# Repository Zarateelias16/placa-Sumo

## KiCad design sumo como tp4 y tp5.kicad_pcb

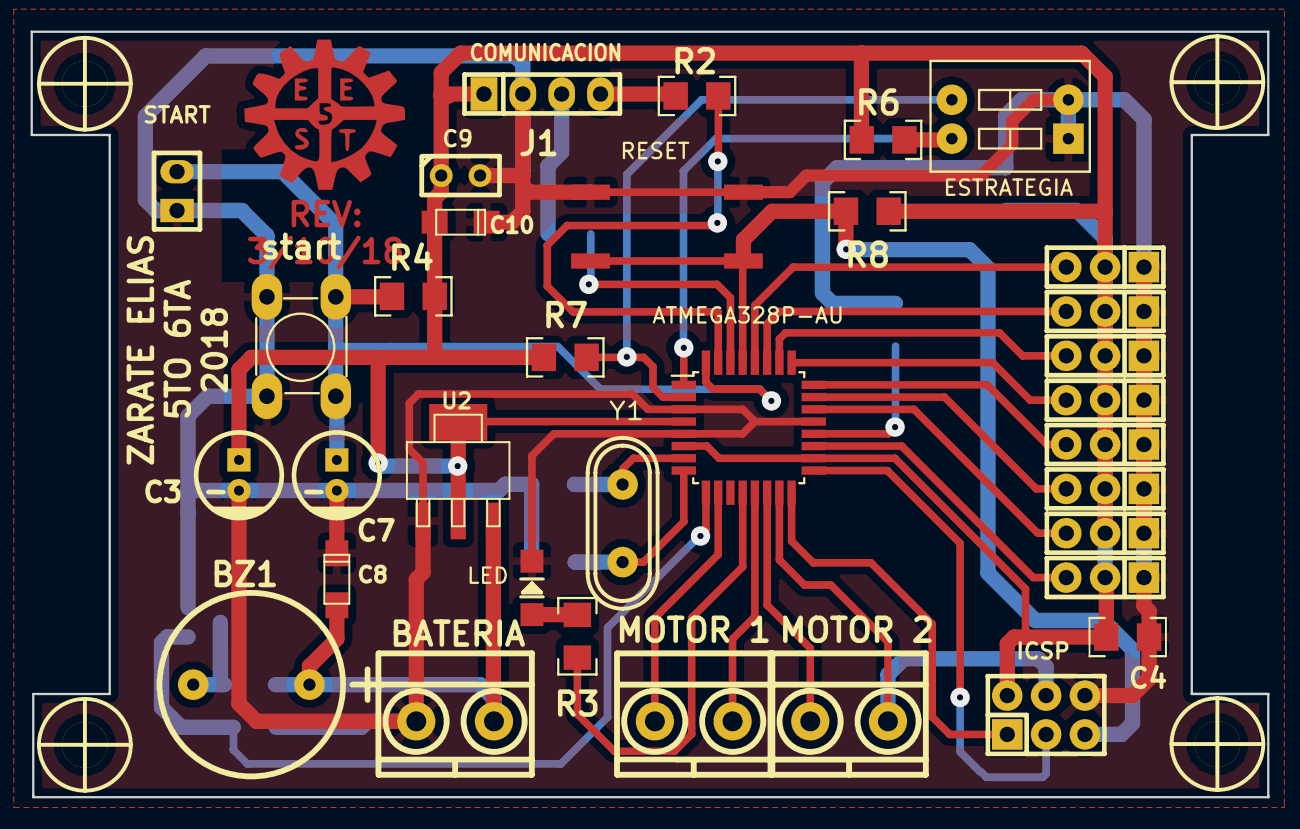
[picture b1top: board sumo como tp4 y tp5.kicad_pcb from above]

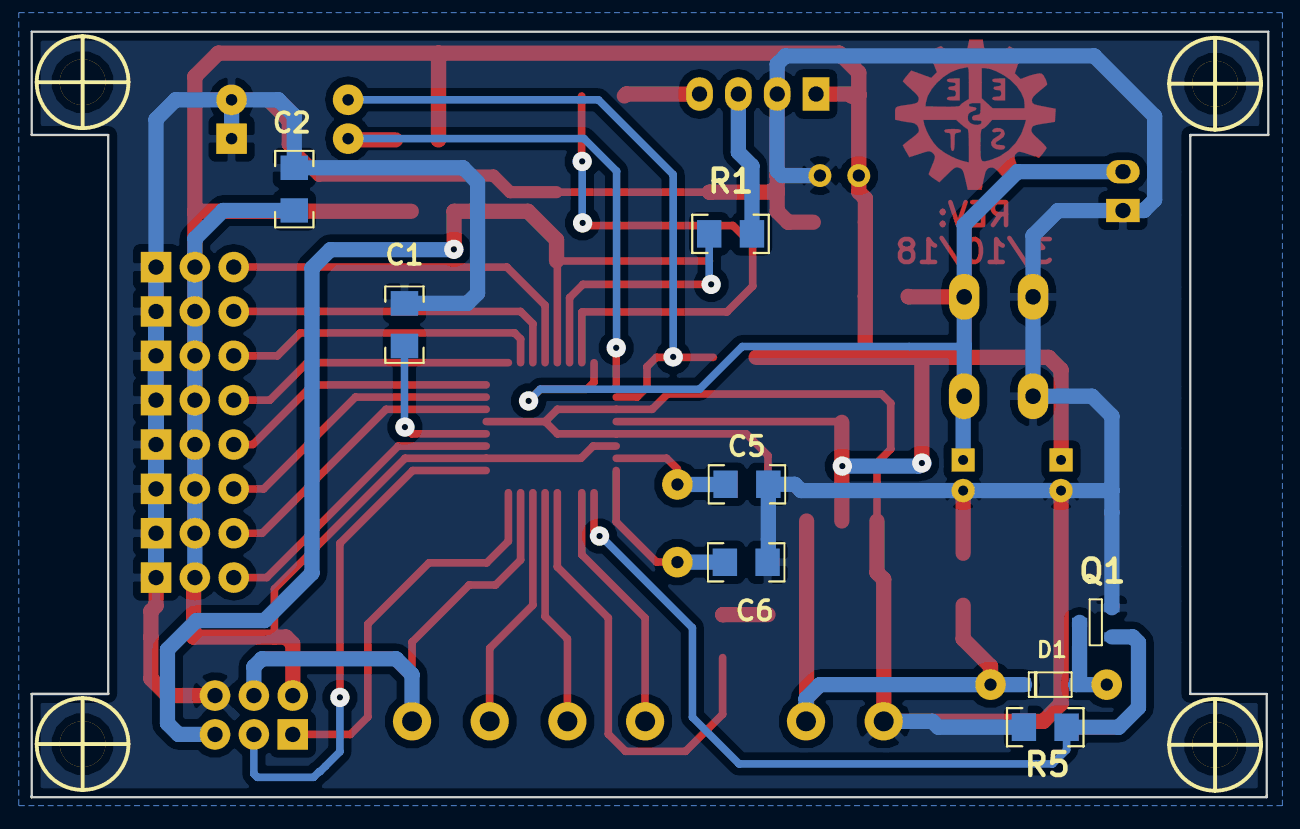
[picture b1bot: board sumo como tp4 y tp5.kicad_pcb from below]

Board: 2 copper layers, 80.9 x 50.0 mm, 46 parts (8 on the bottom side), 32 nets.

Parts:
ATMEGA328P-AU: ATMEGA328P-AU; TQFP-32_7x7mm_Pitch0.8mm
BZ1: Buzzer; Buzzer_12mm
C1: 100nf; C_1206
C2, C4: 1uf; C_1206
C3: 4,7uf; CAP_ELEC_5x11mm
C5, C6: C; C_1206
C7: 10uf; CAP_ELEC_5x11mm
C8, C10: 10uf; CAP_TAN_A
C9: 100nf; CAP_0.1
D1: 1n4148; sod123
ESTRATEGIA: ESTRATEGIA; Dip_SW_2-300
ICSP: HEADER_3x2; pin_strip_3x2
J1: COMUNICACION; pin_strip_4
J3: BATERIA; BORNERA2_AZUL
J4, J7, J11, J12: sharp; Pin_Strip_3
J5, J8, J10, J13: tatami; Pin_Strip_3
J6: MOTOR 1; BORNERA2_AZUL
J9: MOTOR 2; BORNERA2_AZUL
LED: ROJO; LED_1206
Q1: 2N7002; SOT23
R1, R2, R3: 1K; R_1206
R4, R6, R7: 4k7; R_1206
R5: 10k; R_1206
R8: 1k; R_1206
RESET: RESET; Pulsador_4_SMD
START: HEADER_2; Pin_strip_2
SW1: start; Pulsador_TH_4
U2: LM1117-SOT; SOT223
Y1: HC49
hole_3mm, hole_3mm#2, hole_3mm#3, hole_3mm#4: VAL**; hole_3mm

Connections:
+5V: ATMEGA328P-AU.4, ATMEGA328P-AU.6, ATMEGA328P-AU.18, C2.2, C3.1, C4.2, C9.1, C10.1, ICSP.2, J1.1, J4.2, J5.2, J7.2, J8.2, J10.2, J11.2, J12.2, J13.2, R4.1, R6.1, R7.1, R8.1, U2.2, U2.4
/A6: ATMEGA328P-AU.19, J10.3
/A7: ATMEGA328P-AU.22, J4.3
/BUZZER: ATMEGA328P-AU.9, Q1.1, R5.1
/D0/RX: J1.3, R1.1
/D1/TX: J1.4, R2.1
/D8: ATMEGA328P-AU.12, R3.2
/D12/MISO: ATMEGA328P-AU.16, ICSP.1
/D13/SCK: ATMEGA328P-AU.17, ICSP.3
/E1: ATMEGA328P-AU.1, ESTRATEGIA.4, R6.2
/E2: ATMEGA328P-AU.2, ESTRATEGIA.3, R7.2
/M1A: ATMEGA328P-AU.13, J6.2
/M1B: ATMEGA328P-AU.10, J6.1
/M2A: ATMEGA328P-AU.15, ICSP.4, J9.2
/M2B: ATMEGA328P-AU.14, J9.1
/RESET: ATMEGA328P-AU.29, ICSP.5, R8.2, RESET.3, RESET.4
/SFD: ATMEGA328P-AU.25, J11.3
/SFI: ATMEGA328P-AU.26, J7.3
/SLD: ATMEGA328P-AU.27, J8.3
/SLI: ATMEGA328P-AU.28, J13.3
/START: ATMEGA328P-AU.32, C7.1, R4.2, START.2, SW1.3, SW1.4
/TFD: ATMEGA328P-AU.23, J5.3
/TFI: ATMEGA328P-AU.24, J12.3
/VIN: BZ1.1, C8.1, D1.2, J3.2, U2.3
GND: ATMEGA328P-AU.3, ATMEGA328P-AU.5, ATMEGA328P-AU.21, C1.2, C2.1, C3.2, C4.1, C5.1, C6.1, C7.2, C8.2, C9.2, C10.2, ESTRATEGIA.1, ESTRATEGIA.2, ICSP.6, J1.2, J3.1, J4.1, J5.1, J7.1, J8.1, J10.1, J11.1, J12.1, J13.1, LED.2, Q1.3, R5.2, RESET.1, RESET.2, START.1, SW1.1, SW1.2, U2.1
unnamed: BZ1.2, D1.1, Q1.2
unnamed: ATMEGA328P-AU.20, C1.1
unnamed: ATMEGA328P-AU.7, C5.2, Y1.1
unnamed: ATMEGA328P-AU.8, C6.2, Y1.2
unnamed: LED.1, R3.1
unnamed: ATMEGA328P-AU.30, R1.2
unnamed: ATMEGA328P-AU.31, R2.2
